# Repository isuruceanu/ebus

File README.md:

# ebus
ebus adapter and related env

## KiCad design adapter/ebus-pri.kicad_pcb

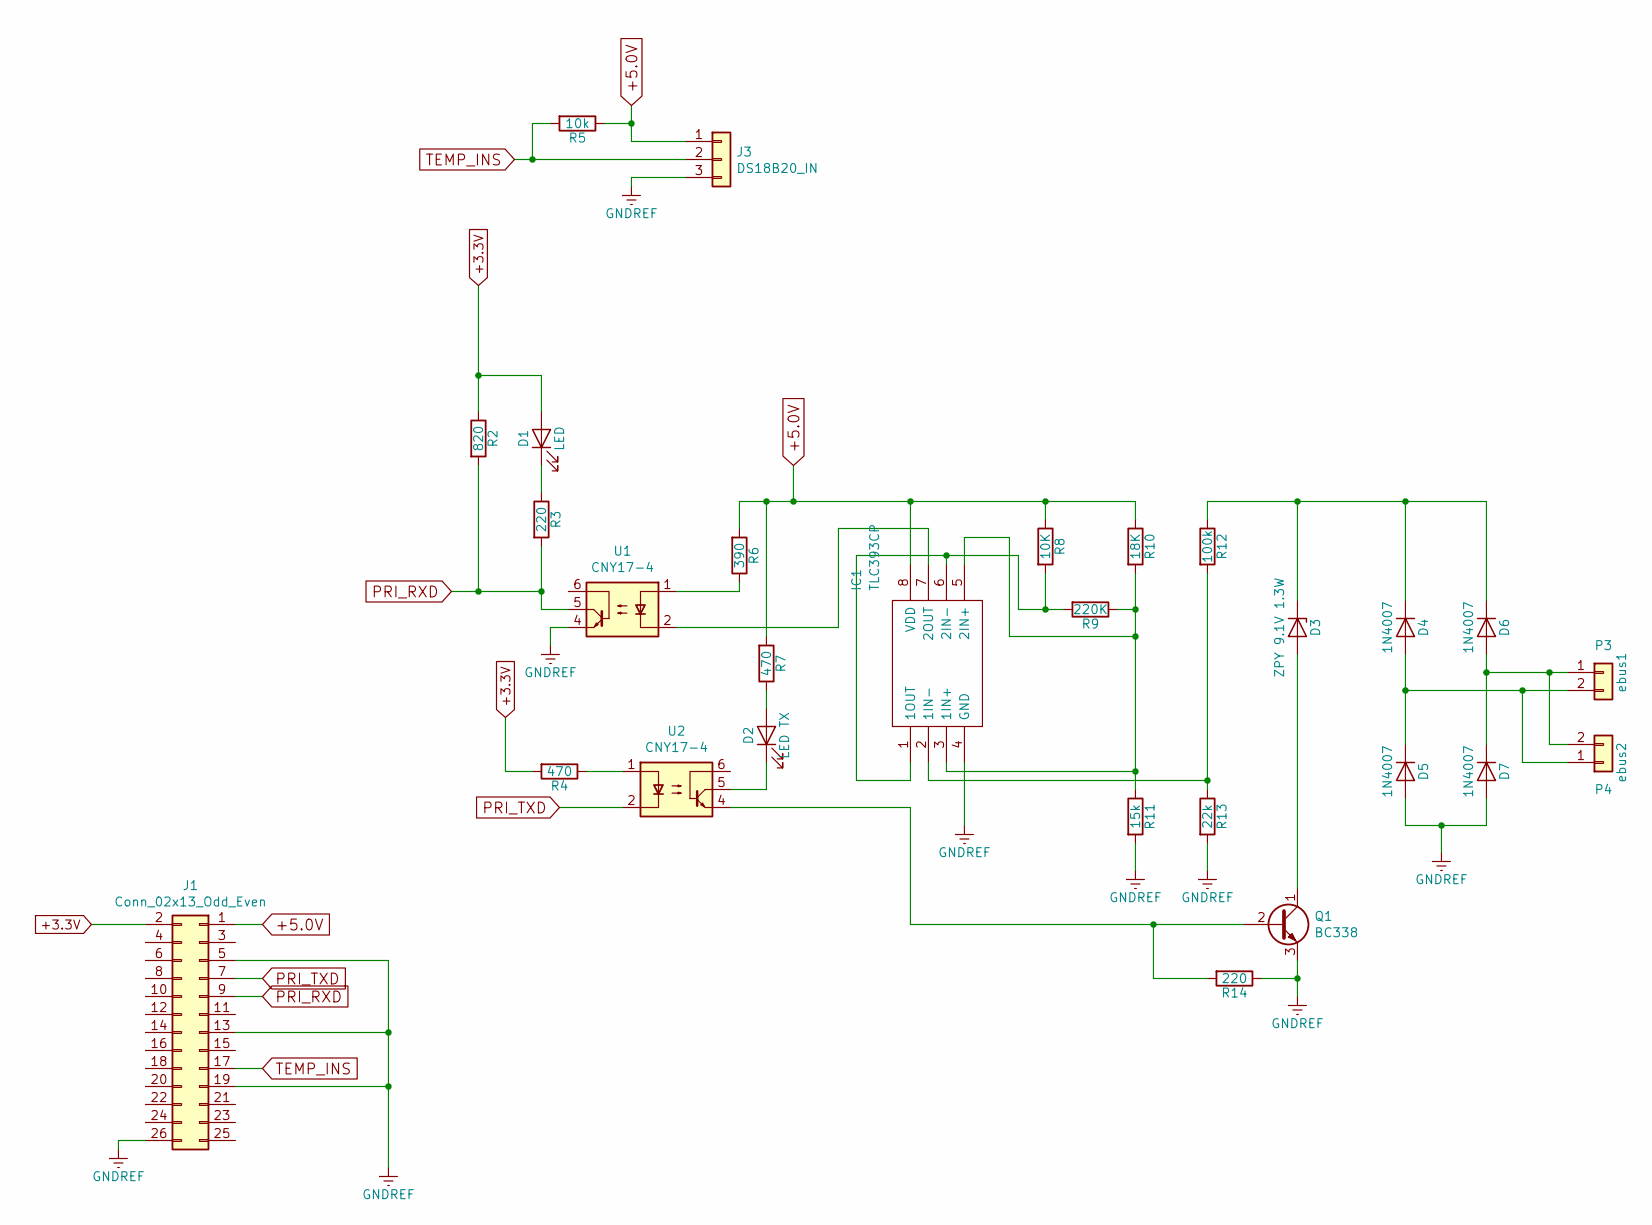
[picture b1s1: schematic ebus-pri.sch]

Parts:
D1: LED; LED_D3.0mm
D2: LED TX; LED_D3.0mm
D3: ZPY 9.1V 1.3W; D_DO-41_SOD81_P2.54mm_Vertical_KathodeUp
D4, D5, D6, D7: 1N4007; D_DO-41_SOD81_P2.54mm_Vertical_KathodeUp
IC1: TLC393CP; DIP794W53P254L959H508Q8N; Manufacturer_Part_Number TLC393CP; Farnell Part Number 3005594
J1: Conn_02x13_Odd_Even; PinHeader_2x13_P2.54mm_Vertical
J3: DS18B20_IN; PinHeader_1x03_P2.54mm_Vertical
P3: ebus1; JWT_A3963_1x02_P3.96mm_Vertical
P4: ebus2; JWT_A3963_1x02_P3.96mm_Vertical
Q1: BC338; TO-92L_Inline_Wide
R2: 820; R_Axial_DIN0207_L6.3mm_D2.5mm_P7.62mm_Horizontal
R3: 220; R_Axial_DIN0207_L6.3mm_D2.5mm_P7.62mm_Horizontal
R4: 470; R_Axial_DIN0207_L6.3mm_D2.5mm_P10.16mm_Horizontal
R5: 10k; R_Axial_DIN0204_L3.6mm_D1.6mm_P2.54mm_Vertical
R6: 390; R_Axial_DIN0204_L3.6mm_D1.6mm_P2.54mm_Vertical
R7: 470; R_Axial_DIN0207_L6.3mm_D2.5mm_P7.62mm_Horizontal
R8: 10K; R_Axial_DIN0204_L3.6mm_D1.6mm_P2.54mm_Vertical
R9: 220K; R_Axial_DIN0204_L3.6mm_D1.6mm_P2.54mm_Vertical
R10: 18K; R_Axial_DIN0207_L6.3mm_D2.5mm_P7.62mm_Horizontal
R11: 15k; R_Axial_DIN0204_L3.6mm_D1.6mm_P2.54mm_Vertical
R12: 100k; R_Axial_DIN0207_L6.3mm_D2.5mm_P2.54mm_Vertical
R13: 22k; R_Axial_DIN0207_L6.3mm_D2.5mm_P2.54mm_Vertical
R14: 220; R_Axial_DIN0207_L6.3mm_D2.5mm_P2.54mm_Vertical
U1, U2: CNY17-4; DIP-6_W7.62mm_LongPads

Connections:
+3.3V: D1.2 (A), J1.2, R2.1, R4.2
+5.0V: IC1.8 (VDD), J1.1, J3.1, R5.1, R6.2, R7.2, R8.1, R10.1
GNDREF: D5.2 (A), D7.2 (A), IC1.4 (GND), J1.5, J1.13, J1.19, J1.26, J3.3, Q1.3 (E), R11.2, R13.2, R14.1, U1.4
unnamed: D1.1 (K), R3.1
unnamed: D2.1 (K), U2.5
unnamed: D2.2 (A), R7.1
unnamed: D3.1 (K), D4.1 (K), D6.1 (K), R12.1
unnamed: D3.2 (A), Q1.1 (C)
unnamed: D4.2 (A), D5.1 (K), P3.2, P4.1
unnamed: D6.2 (A), D7.1 (K), P3.1, P4.2
unnamed: IC1.1 (1OUT), IC1.6 (2IN-), R8.2, R9.2
unnamed: IC1.2 (1IN-), R12.2, R13.1
unnamed: IC1.3 (1IN+), IC1.5 (2IN+), R9.1, R10.2, R11.1
unnamed: IC1.7 (2OUT), U1.2
unnamed: Q1.2 (B), R14.2, U2.4
unnamed: R4.1, U2.1
unnamed: R6.1, U1.1
PRI_RXD: J1.9, R2.2, R3.2, U1.5
PRI_TXD: J1.7, U2.2
TEMP_INS: J1.17, J1.24, J3.2, R5.2

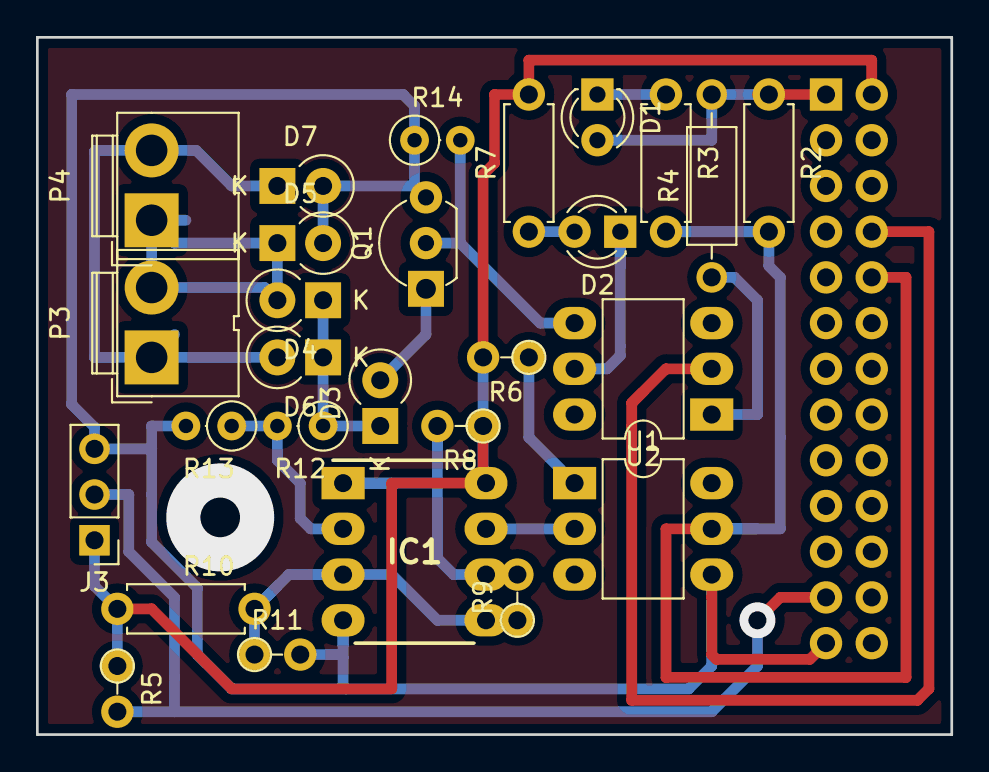
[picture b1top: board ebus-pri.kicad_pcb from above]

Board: 2 copper layers, 50.8 x 38.7 mm, 28 parts (1 on the bottom side), 20 nets.

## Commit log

2019-12-17 ready for print
